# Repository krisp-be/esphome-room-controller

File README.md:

# ESPHome room controller

Open hardware and firmware to light and ventilate the rooms of a house: LED strips in cabinets
and wardrobes, extraction and cabinet fans, presence sensors, door contacts and battery wall
switches. One board per room, programmed with [ESPHome](https://esphome.io). Everything runs on
the board itself, without Home Assistant, a cloud service or an app.

**Do you live in a house with these boards?** Start with [docs/for-new-owners.md](docs/for-new-owners.md).

## What it can do

| | Per controller board |
|---|---|
| Addressable LED strips (24 V) | 4 data lines; each line can drive many strips, every strip or segment separately |
| Fans | 2 PWM channels with speed feedback: mains EC fans (isolated PWM, 1–5 kHz) or 12 V computer fans (25 kHz) |
| Plain 24 V loads | 4 MOSFET outputs, dimmable: white LED strips, solenoids, small fans |
| Sensors | 5 fast inputs (3.3 or 5 V): presence (mmWave), motion (PIR), buttons |
| Contacts and relays | 11 pins on an I/O expander: door and drawer contacts, relay modules |
| Wireless switches | socket for a 4-channel 433 MHz receiver (battery wall switches, no hub) |
| I²C | humidity, VOC, light and other sensors |

An optional **LED distribution board** splits one data line into 8 ports, with power in
parallel and data in series, so a whole wardrobe can be wired neatly.

```
             24 V power supply
                    │
   ┌────────────────┴────────────────┐            ┌──────────────────────────┐
   │        CONTROLLER BOARD         │  STRIP 1   │  LED DISTRIBUTION BOARD  │──► 8 strips
   │  Nano ESP32 + ESPHome           ├───────────►│  (power ∥, data in series)│
   │                                 │  STRIP 2-4 └──────────────────────────┘
   │                                 ├──► strips
   │                                 ├──► fans (PWM + tach), relay ──► mains fan
   │                                 ├──► 24 V loads
   │                                 ◄─── sensors, door contacts, 433 MHz switches
   └─────────────────────────────────┘
```

## Repository

| Folder | Contents |
|---|---|
| [`hardware/`](hardware) | board designs, Gerbers to order them, bills of materials, generator scripts |
| [`esphome/`](esphome) | the firmware: core config, reusable components, example rooms |
| [`docs/`](docs) | wiring guide, troubleshooting, notes for new owners |

## Getting started

1. Order and assemble the boards: [hardware/](hardware).
2. Wire the room: [docs/wiring.md](docs/wiring.md).
3. Write the configuration for the room, starting from an example, and flash it:
   [esphome/](esphome).

## Status

| Part | Status |
|---|---|
| LED distribution board v1 | design finished, ready to order |
| Controller board v2 | connections and pin map fixed, layout in progress |
| ESPHome components and examples | validated and compiled with ESPHome 2025.7 |

## License

[MIT](LICENSE): use, change and share freely, also commercially, at your own risk.
These boards switch 24 V and drive relays that may switch mains voltage: mains wiring must be
done by a qualified person and follow local regulations.

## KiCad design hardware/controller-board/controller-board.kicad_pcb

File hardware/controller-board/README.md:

# Controller board (v2)

> **Status: layout done, not ordered yet.** Fully routed, no DRC errors (only silkscreen warnings).
> Four footprints are still assumptions and must be measured on the real parts first; see
> [Check before ordering](#check-before-ordering). The ESPHome packages in [`esphome/`](../../esphome)
> use the pin map below.

One generic board for every room. It runs on 24 V, carries an Arduino Nano ESP32 running
ESPHome, and drives LED strips, fans, plain 24 V loads, sensors and relays. Whatever a room does
not use stays empty. **No mains voltage on the board:** a mains fan is switched by a separate
relay module, in the same enclosure.

## Blocks

```
24V IN ─┬─ fuse 2 A ×4 ── STRIP 1..4 (+24, GND, DATA)  ◄── 74AHCT125 (3.3→5 V) + 220 Ω ◄── ESP
        ├─ fuse 4 A ───── OUT 1..4 (+24, OUT)          ◄── logic-level MOSFET (+ flyback diode) ◄── ESP PWM
        ├─ step-down 5 V ── 74AHCT125, sensors, relay module, isolated converters
        ├─ step-down 9 V ── Nano ESP32 VIN
        └─ step-down 12 V ─ FAN 1/2 supply for computer fans (FAN V jumper: 12 V or 24 V)

FAN 1/2:  ESP PWM ── 6N137 fast optocoupler ══ PWM, GNDiso  (own isolated 5 V per channel)
          V+, GND, TACH ── 1 kΩ + clamp ── ESP pulse counter   (V+ = 12 V or 24 V, jumper FAN V)
          GND bridge: open = isolated (mains EC fan), fitted = computer fan

IN 1..5:  V, GND, SIG ── 1 kΩ + clamp to 3.3 V ── ESP   (jumper per input: V = 3.3 V or 5 V)

I²C ──┬── MCP23017 (0x20) ── IO A header: A0..A7 (+ GND pins)
      │                    └─ IO B header: B0..B7 (+ GND pins); B3..B7 = 433 MHz receiver socket
      └── I2C terminal (3V3, GND, SDA, SCL), 4.7 kΩ pull-ups on the board
MODULES header: 5V, 5V, 3V3, GND (relay module, other modules)
```

## Connections

| Terminal | Pins | Use | Notes |
|---|---|---|---|
| 24V IN | +, − | 24 V power supply | e.g. Mean Well LRS-150-24 |
| STRIP 1..4 | +24, GND, DATA | addressable 24 V LED strips, or an [LED distribution board](../led-distribution-board) | 2 A fuse (5×20 mm) per output |
| OUT 1..4 | +24, OUT | plain 24 V loads: white LED strip (dimmable), solenoid, small fan | low side switched, shared 4 A fuse |
| FAN 1/2 PWM | PWM, GNDiso | PWM input of the fan | isolated; see GND bridge |
| FAN 1/2 | V+, GND, TACH | power and speed signal of computer fans | V+ = 12 V or 24 V, set with the FAN V jumper |
| FAN V 1/2 (jumper) | 12V / 24V | supply voltage on the FAN terminal | **default 12V**; 24V only for 24 V fans |
| IN 1..5 | V, GND, SIG | presence (mmWave), PIR, buttons, any 3.3/5 V signal | supply jumper per input |
| I2C | 3V3, GND, SDA, SCL | I²C sensors (humidity, VOC, light, …) | |
| IO A / IO B | pin + GND pairs | door and drawer contacts, buttons, relay inputs | MCP23017, 3.3 V logic |
| 433 MHz socket | VT, D0, D1, D2, D3, 3V3, GND | 4-channel 433 MHz receiver module | for battery wall switches |
| MODULES | 5V, 5V, 3V3, GND | power for a relay module and other modules | |

### Fan channels
- **Mains EC fan with a PWM input** (e.g. Ruck EM..EC 02, 1–5 kHz, 5–10 V): connect PWM_In and its GND to
  `PWM` and `GNDiso`, leave the **GND bridge open**. The mains of the fan goes through a relay.
- **4-pin computer fan** (25 kHz): V+, GND and TACH on the FAN terminal, the PWM wire on `PWM`,
  **fit the GND bridge**. Two fans in parallel: connect only one tach wire. Keep the current below 1 A per channel.
- **FAN V jumper:** cap on `12V` (default) for 12 V fans, on `24V` for 24 V PWM fans
  (e.g. Noctua industrialPPC-24V; same PWM and tach standard). **A 12 V fan burns out on 24 V.**

## Pin map (Arduino Nano ESP32)

ESPHome uses the GPIO numbers.

| Nano pin | GPIO | Function |
|---|---|---|
| D12, D10, D9, D11 | 47, 21, 18, 38 | STRIP 1, 2, 3, 4 data |
| A3, A7 | 4, 14 | FAN 1, 2 PWM (inverted by the optocoupler) |
| A0, A6 | 1, 13 | FAN 1, 2 TACH |
| D8, D7, D6, D5 | 17, 10, 9, 8 | OUT 1, 2, 3, 4 (MOSFET gates) |
| D4, D3, D2, D0, D1 | 7, 6, 5, 44, 43 | IN 1, 2, 3, 4, 5 (IN 1..3 also analog) |
| A4, A5 | 11, 12 | I²C SDA, SCL |
| A1 | 2 | MCP23017 interrupt (reserved) |
| D13 | 48 | status LED |
| A2 | 3 | not used (strapping pin) |

MCP23017 pins in ESPHome: A0..A7 = 0..7, B0..B7 = 8..15.
433 MHz receiver: D0 = B4 (12), D1 = B5 (13), D2 = B6 (14), D3 = B7 (15), VT = B3 (11).

## Limits
- ESP32-S3: 4 RMT channels, so **4 data lines** at most. One line can drive many strips in
  series; split it into zones in ESPHome with `partition`.
- 8 PWM channels: 2 fans + 4 MOSFET outputs = 6 used.
- Total current: limited by the power supply (LRS-150-24: 6.5 A).

## Bill of materials (per board)

Fit only what a room uses. **Minimum** = needed on every board (Nano, power, level shifter,
expander). The other groups are per function.

| Ref | Part | Qty | Group | Notes |
|---|---|---|---|---|
| U1 | Arduino Nano ESP32 (ABX00083/ABX00092) | 1 | minimum | on 2 × female header 1 × 15 |
| U2 | Mini560-PRO step-down **9 V** | 1 | minimum | Nano VIN; on pin headers (tracks run underneath) |
| U3 | Mini560-PRO step-down **5 V** | 1 | minimum | 74AHCT125, sensors, relay module, isolated converters |
| U4 | SN74AHCT125N, DIP-14 | 1 | minimum | in a socket |
| U9 | MCP23017-E/SP, DIP-28 | 1 | minimum | I/O expander at 0x20, in a socket |
| C1, C2 | electrolytic 47 µF / 50 V, Ø 6.3 mm | 2 | minimum | 24 V input |
| C4 | electrolytic 220 µF / 25 V, Ø 8 mm | 1 | minimum | 5 V rail |
| C3, C5, C8 | ceramic 100 nF (104), 5 mm pitch | 3 | minimum | |
| R33, R34 | 4.7 kΩ | 2 | minimum | I²C pull-ups |
| J1 | screw terminal 2 poles, 5.08 mm | 1 | minimum | 24 V in |
| J11, J13 | screw terminal 2 poles, 5.08 mm | 2 | I²C | |
| J18, J12 | pin header 2 × 8, 2.54 mm | 2 | IO A / IO B | odd row = IO, even row = GND |
| J7 | pin header 1 × 4, 2.54 mm | 1 | modules | 5V, 5V, 3V3, GND |
| U6 | female header 1 × 7, 2.54 mm | 1 | 433 MHz | receiver socket |
| J2–J5 | screw terminal 3 poles, 5.08 mm | 4 | strips | per strip |
| F1–F4 | fuse holder 5 × 20 mm, PCB + fuse 2 A | 4 | strips | per strip |
| R1–R4 | 220 Ω | 4 | strips | series resistor in the data line |
| R10–R13 | 10 kΩ | 4 | strips | pull-down: strips stay dark while the ESP boots |
| J14–J17 | screw terminal 2 poles, 5.08 mm | 4 | OUT | per output |
| Q1–Q4 | IRLZ44N (logic level, TO-220) | 4 | OUT | per output |
| D1–D4 | 1N5819 | 4 | OUT | flyback diode |
| R20–R23, R24–R27 | 100 Ω, 10 kΩ | 4 + 4 | OUT | gate resistor, gate pull-down |
| F5 | fuse holder 5 × 20 mm + fuse 4 A | 1 | OUT | shared by OUT 1..4 |
| U5 / U10 | HLK-1D0505A isolated 5 V | 1 | per fan | |
| U7 / U11 | 6N137, DIP-8 | 1 | per fan | in a socket; the EL817/PC817 is too slow for 25 kHz |
| R5 / R7 | 180 Ω (220 Ω works too) | 1 | per fan | LED current 6N137 |
| R6 / R8 | 2.2 kΩ | 1 | per fan | pull-up of PWM to the isolated 5 V |
| C9 / C10 | ceramic 100 nF | 1 | per fan | |
| J6 / J9 | screw terminal 2 poles | 1 | per fan | PWM, GNDiso |
| J19 / J20 | screw terminal 3 poles | 1 | per fan | V+, GND, TACH |
| R15 / R16, D5 / D6 | 1 kΩ, 1N5819 (or BAT85) | 1 + 1 | per fan | tach protection |
| JP6 / JP7 | pin header 1 × 3 + jumper cap | 1 | per fan | FAN V: 12 V or 24 V |
| W1 / W2 | wire bridge (resistor leg) | 0–1 | per fan | **only** for computer fans |
| U8 | Mini560-PRO step-down **12 V** | 1 | 12 V fans | not needed for mains or 24 V fans |
| C7 | electrolytic 220 µF / 25 V | 1 | 12 V fans | |
| J22–J26 | screw terminal 3 poles | 1 | per input | V, GND, SIG |
| JP1–JP5 | pin header 1 × 3 + jumper cap | 1 | per input | input supply 3.3 V or 5 V |
| R28–R32, D7–D11 | 1 kΩ, 1N5819 (or BAT85) | 1 + 1 | per input | input protection |
| H1–H4 | M3 mounting holes | 4 | | |

The clamp diodes have DO-41 holes, so both a 1N5819 and a BAT85 fit.

## Ordering

[`fabrication/controller-board-gerbers.zip`](fabrication/controller-board-gerbers.zip):
2 layers, **170 × 110 mm**, FR-4, 1.6 mm, 1 oz copper, HASL, white silkscreen, 5 pieces.
Order it together with the [LED distribution board](../led-distribution-board) to share the
shipping cost.

### Check before ordering
Measured on the real parts (2026-11): Mini560-PRO (33 x 18.2 mm, connections in the corners), 433 MHz
receiver pin order, fuse holder (flat legs, 22.6 mm, holes enlarged to 1.8 mm), screw terminals,
capacitors and the Nano row spacing. Still to confirm:
1. **Mini560-PRO** (U2, U3, U8): IN+ and OUT+ along the **same** long edge (assumed). Mount each module
   on 4 single header pins, one per connection: tracks run underneath.
2. **Hi-Link isolated 5 V** (U5, U10; delivered as B0505S-1WR3): pin order confirmed (dot = pin 1,
   diode test): 1 −Vin, 2 +Vin, 3 −Vout, 4 +Vout. Pin 1 (dot, left when you read the text) goes in the
   square pad.
3. **433 MHz receiver** (U6): the module is 28.3 mm wide; its four unpinned pads (ST, LED, GND, ANT)
   overhang to the west, past VT. Solder a 17.3 cm wire to ANT if the module has no antenna.

### Isolation
The isolated corners (silkscreen ISOLATED 1/2) have their own GND planes, at least 2 mm away
from the rest. This is **functional** isolation, not reinforced insulation for mains: check that
the PWM input of a mains fan is SELV (safety extra-low voltage).

## Rebuilding

The board is generated from [`parts.py`](parts.py) (placement and netlist) by the scripts in
[`../tools`](../tools): `../tools/make-board.sh ../controller-board` places, routes (each attempt in
its own process), runs the DRC and writes the Gerbers and images.

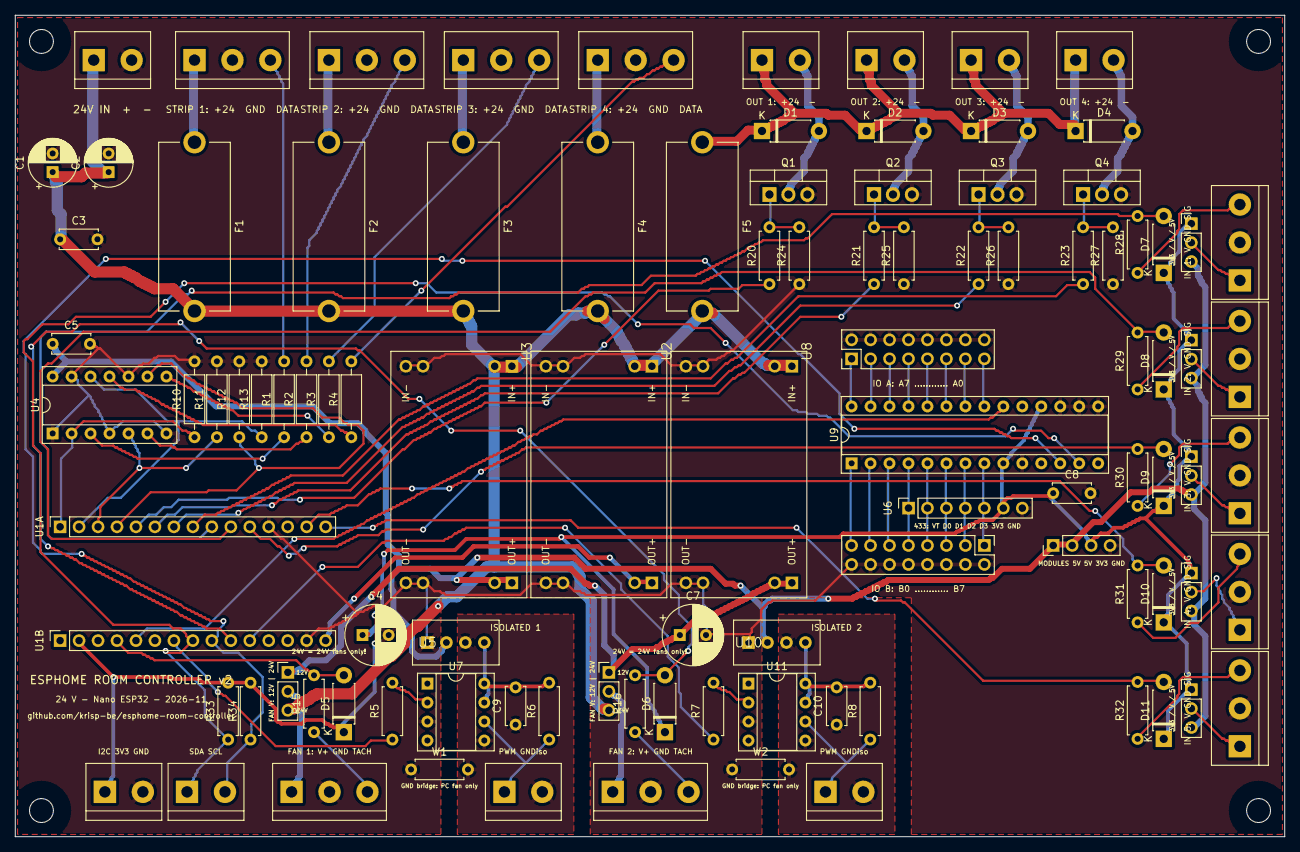
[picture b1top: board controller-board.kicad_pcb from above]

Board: 2 copper layers, 170.0 x 110.0 mm, 106 parts (0 on the bottom side), 85 nets.

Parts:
C1, C2: 47u/50V; CP_Radial_D6.3mm_P2.50mm
C3, C5, C8, C9, C10: 100n; C_Disc_D5.0mm_W2.5mm_P5.00mm
C4, C7: 220u/25V; CP_Radial_D8.0mm_P3.50mm
D1, D2, D3, D4, D5, D6, D7, D8, D9, D10, D11: 1N5819; D_DO-41_SOD81_P7.62mm_Horizontal
F1, F2, F3, F4: 2A; Fuseholder_Cylinder-5x20mm_Stelvio-Kontek_PTF78_Horizontal_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
F5: 4A; Fuseholder_Cylinder-5x20mm_Stelvio-Kontek_PTF78_Horizontal_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
H1, H2, H3, H4: MountingHole_3.2mm_M3
J1: 24V in; TerminalBlock_bornier-2_P5.08mm
J2: STRIP 1; TerminalBlock_bornier-3_P5.08mm
J3: STRIP 2; TerminalBlock_bornier-3_P5.08mm
J4: STRIP 3; TerminalBlock_bornier-3_P5.08mm
J5: STRIP 4; TerminalBlock_bornier-3_P5.08mm
J6: FAN 1 PWM; TerminalBlock_bornier-2_P5.08mm
J7: MODULES; PinHeader_1x04_P2.54mm_Vertical
J9: FAN 2 PWM; TerminalBlock_bornier-2_P5.08mm
J11: I2C power; TerminalBlock_bornier-2_P5.08mm
J12: IO B; PinHeader_2x08_P2.54mm_Vertical
J13: I2C; TerminalBlock_bornier-2_P5.08mm
J14: OUT 1; TerminalBlock_bornier-2_P5.08mm
J15: OUT 2; TerminalBlock_bornier-2_P5.08mm
J16: OUT 3; TerminalBlock_bornier-2_P5.08mm
J17: OUT 4; TerminalBlock_bornier-2_P5.08mm
J18: IO A; PinHeader_2x08_P2.54mm_Vertical
J19: FAN 1; TerminalBlock_bornier-3_P5.08mm
J20: FAN 2; TerminalBlock_bornier-3_P5.08mm
J22: IN 1; TerminalBlock_bornier-3_P5.08mm
J23: IN 2; TerminalBlock_bornier-3_P5.08mm
J24: IN 3; TerminalBlock_bornier-3_P5.08mm
J25: IN 4; TerminalBlock_bornier-3_P5.08mm
J26: IN 5; TerminalBlock_bornier-3_P5.08mm
JP1: IN 1 supply; PinHeader_1x03_P2.54mm_Vertical
JP2: IN 2 supply; PinHeader_1x03_P2.54mm_Vertical
JP3: IN 3 supply; PinHeader_1x03_P2.54mm_Vertical
JP4: IN 4 supply; PinHeader_1x03_P2.54mm_Vertical
JP5: IN 5 supply; PinHeader_1x03_P2.54mm_Vertical
JP6: FAN 1 V: 12V | 24V; PinHeader_1x03_P2.54mm_Vertical
JP7: FAN 2 V: 12V | 24V; PinHeader_1x03_P2.54mm_Vertical
Q1, Q2, Q3, Q4: IRLZ44N; TO-220-3_Vertical
R1, R2, R3, R4: 220; R_Axial_DIN0207_L6.3mm_D2.5mm_P10.16mm_Horizontal
R5, R7: 180; R_Axial_DIN0207_L6.3mm_D2.5mm_P7.62mm_Horizontal
R6, R8: 2k2; R_Axial_DIN0207_L6.3mm_D2.5mm_P7.62mm_Horizontal
R10, R11, R12, R13: 10k; R_Axial_DIN0207_L6.3mm_D2.5mm_P10.16mm_Horizontal
R15, R16, R28, R29, R30, R31, R32: 1k; R_Axial_DIN0207_L6.3mm_D2.5mm_P7.62mm_Horizontal
R20, R21, R22, R23: 100; R_Axial_DIN0207_L6.3mm_D2.5mm_P7.62mm_Horizontal
R24, R25, R26, R27: 10k; R_Axial_DIN0207_L6.3mm_D2.5mm_P7.62mm_Horizontal
R33, R34: 4k7; R_Axial_DIN0207_L6.3mm_D2.5mm_P7.62mm_Horizontal
U1A: Nano ESP32 north; PinSocket_1x15_P2.54mm_Vertical
U1B: Nano ESP32 south; PinSocket_1x15_P2.54mm_Vertical
U2: Mini560 9V
U3: Mini560 5V
U4: 74AHCT125; DIP-14_W7.62mm_Socket
U5, U10: HLK-1D0505A
U6: 433 MHz receiver; PinSocket_1x07_P2.54mm_Vertical
U7, U11: 6N137; DIP-8_W7.62mm_Socket
U8: Mini560 12V
U9: MCP23017; DIP-28_W7.62mm_Socket
W1, W2: GND bridge; R_Axial_DIN0207_L6.3mm_D2.5mm_P7.62mm_Horizontal

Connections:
+3V3: C8.1, D5.1, D6.1, D7.1, D8.1, D9.1, D10.1, D11.1, J7.3, J11.1, JP1.1, JP2.1, JP3.1, JP4.1, JP5.1, R33.2, R34.2, U1B.2, U6.6, U9.9, U9.18
+5V: C4.1, C5.1, J7.1, J7.2, JP1.3, JP2.3, JP3.3, JP4.3, JP5.3, U3.3, U4.14, U5.2, U10.2
+5VISO1: C9.2, R6.2, U5.4, U7.7, U7.8
+5VISO2: C10.2, R8.2, U10.4, U11.7, U11.8
+9V: U1B.15, U2.3
+12V: C7.1, JP6.1, JP7.1, U8.3
+24V: C1.1, C2.1, C3.1, F1.2, F2.2, F3.2, F4.2, F5.2, J1.1, JP6.3, JP7.3, U2.1, U3.1, U8.1
+24V_M: D1.1, D2.1, D3.1, D4.1, F5.1, J14.1, J15.1, J16.1, J17.1
+24V_S1: F1.1, J2.1
+24V_S2: F2.1, J3.1
+24V_S3: F3.1, J4.1
+24V_S4: F4.1, J5.1
BUF1: R1.1, U4.3
BUF2: R2.1, U4.6
BUF3: R3.1, U4.8
BUF4: R4.1, U4.11
DATA1: J2.3, R1.2
DATA2: J3.3, R2.2
DATA3: J4.3, R3.2
DATA4: J5.3, R4.2
D_S1: R10.1, U1A.1, U4.2
D_S2: R11.1, U1A.3, U4.5
D_S3: R12.1, U1A.4, U4.9
D_S4: R13.1, U1A.2, U4.12
FAN1_V: J19.1, JP6.2
FAN2_V: J20.1, JP7.2
G1: Q1.1, R20.2, R24.2
G2: Q2.1, R21.2, R25.2
G3: Q3.1, R22.2, R26.2
G4: Q4.1, R23.2, R27.2
GND: C1.2, C2.2, C3.2, C4.2, C5.2, C7.2, C8.2, J1.2, J2.2, J3.2, J4.2, J5.2, J7.4, J11.2, J12.2, J12.4, J12.6, J12.8, J12.10, J12.12, J12.14, J12.16, J18.2, J18.4, J18.6, J18.8, J18.10, J18.12, J18.14, J18.16, J19.2, J20.2, J22.2, J23.2, J24.2, J25.2, J26.2, Q1.3, Q2.3, Q3.3, Q4.3, R10.2, R11.2, R12.2, R13.2, R24.1, R25.1, R26.1, R27.1, U1A.12, U1B.14, U2.2, U2.4, U3.2, U3.4, U4.1, U4.4, U4.7, U4.10, U4.13, U5.1, U6.7, U7.3, U8.2, U8.4, U9.10, U9.15, U9.16, U9.17, U10.1, U11.3, W1.1, W2.1
GNDISO1: C9.1, J6.2, U5.3, U7.5, W1.2
GNDISO2: C10.1, J9.2, U10.3, U11.5, W2.2
IN1: D7.2, R28.2, U1A.9
IN1_IN: J22.3, R28.1
IN2: D8.2, R29.2, U1A.10
IN2_IN: J23.3, R29.1
IN3: D9.2, R30.2, U1A.11
IN3_IN: J24.3, R30.1
IN4: D10.2, R31.2, U1A.14
IN4_IN: J25.3, R31.1
IN5: D11.2, R32.2, U1A.15
IN5_IN: J26.3, R32.1
INT: U1B.5, U9.20
IOA0: J18.15, U9.21
IOA1: J18.13, U9.22
IOA2: J18.11, U9.23
IOA3: J18.9, U9.24
IOA4: J18.7, U9.25
IOA5: J18.5, U9.26
IOA6: J18.3, U9.27
IOA7: J18.1, U9.28
IOB0: J12.15, U9.1
IOB1: J12.13, U9.2
IOB2: J12.11, U9.3
IOB3: J12.9, U6.1, U9.4
IOB4: J12.7, U6.2, U9.5
IOB5: J12.5, U6.3, U9.6
IOB6: J12.3, U6.4, U9.7
IOB7: J12.1, U6.5, U9.8
MOS1: R20.1, U1A.5
MOS2: R21.1, U1A.6
MOS3: R22.1, U1A.7
MOS4: R23.1, U1A.8
OPTO1_A: R5.2, U7.2
OPTO2_A: R7.2, U11.2
OUT1: D1.2, J14.2, Q1.2
OUT2: D2.2, J15.2, Q2.2
OUT3: D3.2, J16.2, Q3.2
OUT4: D4.2, J17.2, Q4.2
PWM1: R5.1, U1B.7
PWM2: R7.1, U1B.11
PWM_OUT1: J6.1, R6.1, U7.6
PWM_OUT2: J9.1, R8.1, U11.6
SCL: J13.2, R34.1, U1B.9, U9.12
SDA: J13.1, R33.1, U1B.8, U9.13
TACH1: D5.2, R15.2, U1B.4
TACH1_IN: J19.3, R15.1
TACH2: D6.2, R16.2, U1B.10
TACH2_IN: J20.3, R16.1
VIN1: J22.1, JP1.2
VIN2: J23.1, JP2.2
VIN3: J24.1, JP3.2
VIN4: J25.1, JP4.2
VIN5: J26.1, JP5.2

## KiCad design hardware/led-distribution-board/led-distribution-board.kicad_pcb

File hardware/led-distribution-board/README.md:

# LED distribution board (8 ports)

Version 1, 2026-11. Connects up to 8 separate LED strips to **one** data line of the controller
board: power goes to every strip in parallel, the data runs through the strips in series.
Boards can be chained for more strips.

## How it works

```
             ┌─ port 1: +24 · GND · DI ──► strip ──► DO ─┐
IN DATA ─────┘                                           │
             ┌───────────────────────────────────────────┘
             └─ port 2 … port 8 ──► DO ──► OUT DATA (to the next board)

24V IN ──┬── PTC ── port 1 +24
         ├── PTC ── port 2 +24      (parallel, each with its own resettable fuse)
         └── …
```

- **Power in parallel:** +24 V and GND go to every port, each through its own PTC.
- **Data in series:** DO of port k is connected to DI of port k+1. In ESPHome the whole line is
  one strip; split it into one zone per strip with a `partition` light
  (see [`walk-in-closet.yaml`](../../esphome/examples/walk-in-closet.yaml)).
- **Empty port:** fit the jumper **bridge=empty**. It connects DI to DO so the data passes.
  **Never fit that jumper on a port with a strip:** two outputs would then drive the same line.
- **Pull-out parts** (shelves with pogo connectors): always on the last used port of the chain.
  A removed part interrupts the data for everything after it.

Each strip needs **4 wires**: out +24, GND and DI, and back DO from the end of the strip.
A 4-core cable (e.g. LiYY 4 × 0.5 mm²) is easiest.

## Connections

| Terminal | Pins (left to right / top to bottom) | Use |
|---|---|---|
| Ports 1–8 | +24, GND, DI, DO | the strips |
| 24V IN (left) | +, − | power of the board, thick wire (1.5 mm²) straight from the power supply |
| IN (left) | +24, GND, DATA | data from the controller board (same order as its STRIP outputs) |
| OUT (right) | +24, GND, DATA | data to the next board |

Jumpers:

| Jumper | Fitted | Open (default) |
|---|---|---|
| JP1–JP8 **bridge=empty** | port empty, data passes | a strip is connected |
| JP9 **24V via IN** | the board is powered through the STRIP output of the controller board (max. 2 A, its fuse); leave 24V IN empty | powered through 24V IN |
| JP10 **24V to OUT** | the next board is powered through this one (small setups only) | only data and GND to OUT |

**Chain the data, not the power:** give every board its own 24 V on 24V IN. GND always goes
along through IN and OUT, because the data signal needs a common ground.

Ports 1–4 are at the top, 5–8 at the bottom. The chain runs 1 → 4, then across the board to 5,
and on to 8 → OUT.

## Current

- The +24 V plane covers the front and the GND plane the back, over the whole board. Pads are
  connected solidly (no thermal spokes), so the planes carry about 6 A: the full output of an
  LRS-150-24. Soldering takes a bit longer: use a hot iron.
- Per port: a 1.1 A PTC (hold current). 1 m of 24 V RGBW strip at full white draws about 0.7 A.
  For a longer strip on one port, use a 1.6 A PTC.

## Bill of materials (per board)

| Ref | Part | Qty | Notes |
|---|---|---|---|
| J1–J8 | screw terminal, 4 poles, 5.08 mm | 8 | or 2 × 2 poles slid together; push-in terminals with 5.0/5.08 mm pitch fit too (1.5 mm holes) |
| J9 | screw terminal, 2 poles, 5.08 mm | 1 | |
| J10, J11 | screw terminal, 3 poles, 5.08 mm | 2 | |
| F1–F8 | radial PTC, **≥ 30 V**, 1.1 A hold, leads 5.0–5.1 mm apart | 8 | e.g. Littelfuse RXEF110 (72 V) or Bourns MF-R110 (30 V) |
| JP1–JP10 | pin header 1 × 2, 2.54 mm + jumper cap | 10 | |
| C1 | electrolytic 47 µF / 50 V, Ø 8 mm, 3.5 mm pitch | 1 | |
| R1 | 4.7 kΩ, 0.25 W | 1 | about 5 mA for the LED |
| D1 | LED 3 mm | 1 | on when 24 V is present |
| H1–H4 | M3 mounting holes | 4 | copper-free ring of Ø 8 mm around each hole |

## Ordering

[`fabrication/led-distribution-board-gerbers.zip`](fabrication/led-distribution-board-gerbers.zip):
2 layers, **100 × 80 mm**, FR-4, 1.6 mm, 1 oz copper (2 oz for extra current margin), HASL,
white silkscreen. Order it together with the controller board to share the shipping cost.

Check before ordering: PTC lead spacing (5.0–5.1 mm, leads up to about 0.7 mm thick); with
push-in terminals, their pitch (5.0 or 5.08 mm) and pin size (1.5 mm holes).

## Rebuilding

The board is generated from [`parts.py`](parts.py) (placement and netlist) by the scripts in
[`../tools`](../tools): `../tools/make-board.sh .` places, routes, runs the DRC and writes the
Gerbers and images.

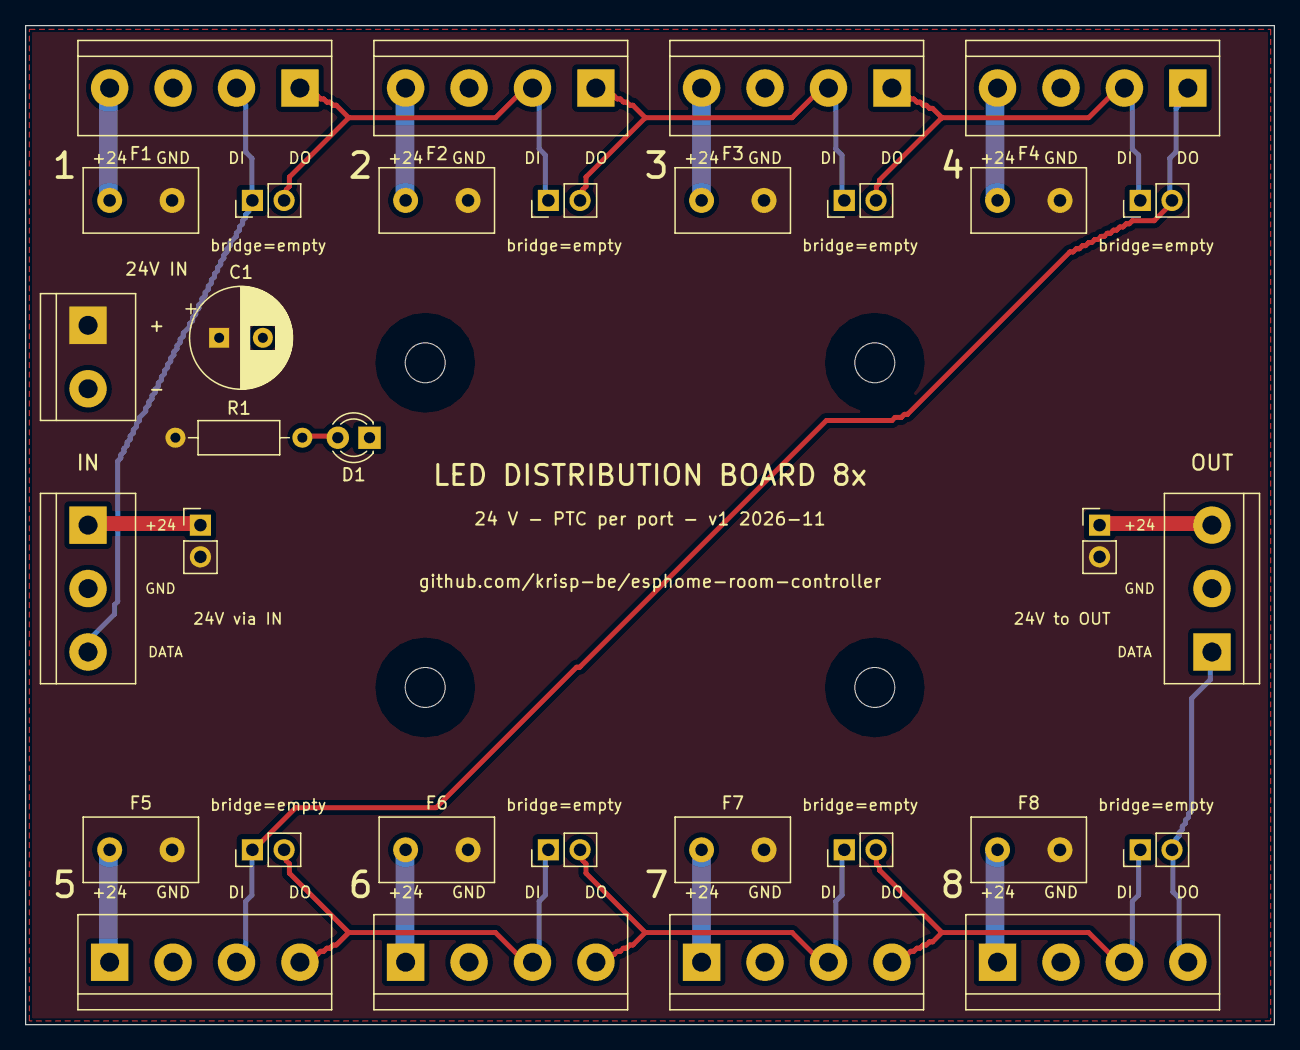
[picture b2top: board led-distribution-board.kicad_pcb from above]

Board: 2 copper layers, 100.0 x 80.0 mm, 36 parts (0 on the bottom side), 22 nets.

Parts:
C1: 47u/50V; CP_Radial_D8.0mm_P3.50mm
D1: LED 24V; LED_D3.0mm
F1, F2, F3, F4, F5, F6, F7, F8: PTC 1.1A; C_Disc_D9.0mm_W5.0mm_P5.00mm
H1, H2, H3, H4: MountingHole_3.2mm_M3
J1: port 1; TerminalBlock_bornier-4_P5.08mm
J2: port 2; TerminalBlock_bornier-4_P5.08mm
J3: port 3; TerminalBlock_bornier-4_P5.08mm
J4: port 4; TerminalBlock_bornier-4_P5.08mm
J5: port 5; TerminalBlock_bornier-4_P5.08mm
J6: port 6; TerminalBlock_bornier-4_P5.08mm
J7: port 7; TerminalBlock_bornier-4_P5.08mm
J8: port 8; TerminalBlock_bornier-4_P5.08mm
J9: 24V in; TerminalBlock_bornier-2_P5.08mm
J10: IN; TerminalBlock_bornier-3_P5.08mm
J11: OUT; TerminalBlock_bornier-3_P5.08mm
JP1, JP2, JP3, JP4, JP5, JP6, JP7, JP8: bridge if empty; PinHeader_1x02_P2.54mm_Vertical
JP9: 24V via IN; PinHeader_1x02_P2.54mm_Vertical
JP10: 24V to OUT; PinHeader_1x02_P2.54mm_Vertical
R1: 4k7; R_Axial_DIN0207_L6.3mm_D2.5mm_P10.16mm_Horizontal

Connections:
+24V: C1.1, F1.2, F2.2, F3.2, F4.2, F5.2, F6.2, F7.2, F8.2, J9.1, JP9.2, JP10.2, R1.1
+24V_IN: J10.1, JP9.1
+24V_OUT: J11.3, JP10.1
+24V_P1: F1.1, J1.4
+24V_P2: F2.1, J2.4
+24V_P3: F3.1, J3.4
+24V_P4: F4.1, J4.4
+24V_P5: F5.1, J5.1
+24V_P6: F6.1, J6.1
+24V_P7: F7.1, J7.1
+24V_P8: F8.1, J8.1
D1: J1.1, J2.2, JP1.2, JP2.1
D2: J2.1, J3.2, JP2.2, JP3.1
D3: J3.1, J4.2, JP3.2, JP4.1
D4: J4.1, J5.3, JP4.2, JP5.1
D5: J5.4, J6.3, JP5.2, JP6.1
D6: J6.4, J7.3, JP6.2, JP7.1
D7: J7.4, J8.3, JP7.2, JP8.1
DATA_IN: J1.2, J10.3, JP1.1
DATA_OUT: J8.4, J11.1, JP8.2
GND: C1.2, D1.1, J1.3, J2.3, J3.3, J4.3, J5.2, J6.2, J7.2, J8.2, J9.2, J10.2, J11.2
LED_A: D1.2, R1.2
